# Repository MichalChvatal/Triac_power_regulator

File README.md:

# AVR Triac Regulator (ATtiny13)

---

## ⚠️ Safety Disclaimer

This project involves **AC mains voltage**, which is **extremely dangerous** and can cause **serious injury or death**.  

By using this project, you accept **full responsibility** for any accidents, injuries, or damages. The author is **not liable** for any consequences resulting from its use.  

**Important Safety Guidelines:**
- Always use insulated tools and protective equipment.
- Work with a qualified professional if you are inexperienced with mains circuits.
- Use galvanic isolation (optotriacs/optocouplers) wherever possible.
- **Do not proceed** if you are unfamiliar with handling high voltage.

---

## Project Overview

This project implements a **power regulator for universal commutator motors** (motors with brushes) and resistive loads (e.g., light bulbs and heating elements) using the **ATtiny13** microcontroller.  
It provides **0–100% power control** through **phase-angle control of a triac** with **AC mains zero-cross detection**.

⚠️ **Warning:** The circuit connects directly to **230 V mains**. Extreme caution is required during assembly and testing.

---

## ✨ Features
- Measurement of the delay between zero-crossing and triac triggering.
- Adjustable firing angle using a potentiometer (or DIP switch).
- Generation of a trigger pulse for the optotriac in every half cycle.
- Motor power control from **fully OFF (0%)** to **fully ON (100%)**.

---

## 🧩 Components

### Triac driver (optotriac)
Must be of the **random-phase type** (no built-in zero-cross detection), e.g.:
- `MOC3021`
- `MOC3010`

### Zero-cross detector
The output must be a **rectangular pulse signal** for reliable edge detection by the MCU, e.g.:
- `H11L1` (recommended)

If using slower optocouplers such as `4N35`, you must add a **Schmitt trigger** circuit to clean up the signal.

### Microcontroller
- `ATtiny13` (or alternatively `ATmega8`)

### Firing angle adjustment
- **Potentiometer** (connected to ADC input)  
- or **DIP switch** (digital inputs)

---

## ⚡ Safety notes
- This regulator is suitable only for **universal commutator motors (brush motors)** and **resistive loads** (e.g., light bulbs and heating elements).
- It is **not suitable for asynchronous (induction) motors**.  
- The motor must **not** have its own built-in electronic regulation.  
- The motor must use **series excitation**.

---

## 🛠️ Project directory structure

- **HW/** – Eagle PCB design files (.sch, .brd)
- **SW/**  - Atmel Studio project files (.cproj, .atsln), Doxyfile
  - **src/** – Source files (.c)
  - **inc/** – Header files (.h)
  - **docs/** – Generated documentation (Doxygen)

---

## ⚙️ Fuse and clock configuration

- Set fuses for **internal oscillator 4.8 MHz**:  
  - **Low fuse:** `0x79`  
  - **High fuse:** `0xFF`  
- ⚠️ **Calibration is required** – see ATtiny13 datasheet for details.  
- Note: `clk I/O` = `clk CPU`. The difference is that during sleep mode, **I/O clocks are disabled**, while CPU/peripheral clocks may continue to run.

--- 

## 🔧 Building the Project
To build the project, launch the **Regulator.atsln** file with **Microchip Studio (version 7.0.2594)**.

- From the menu bar, select Build > Build Solution.
-  Alternatively, use the shortcut F7.

The output files will be located in the project's **Debug** or **Release** folder.

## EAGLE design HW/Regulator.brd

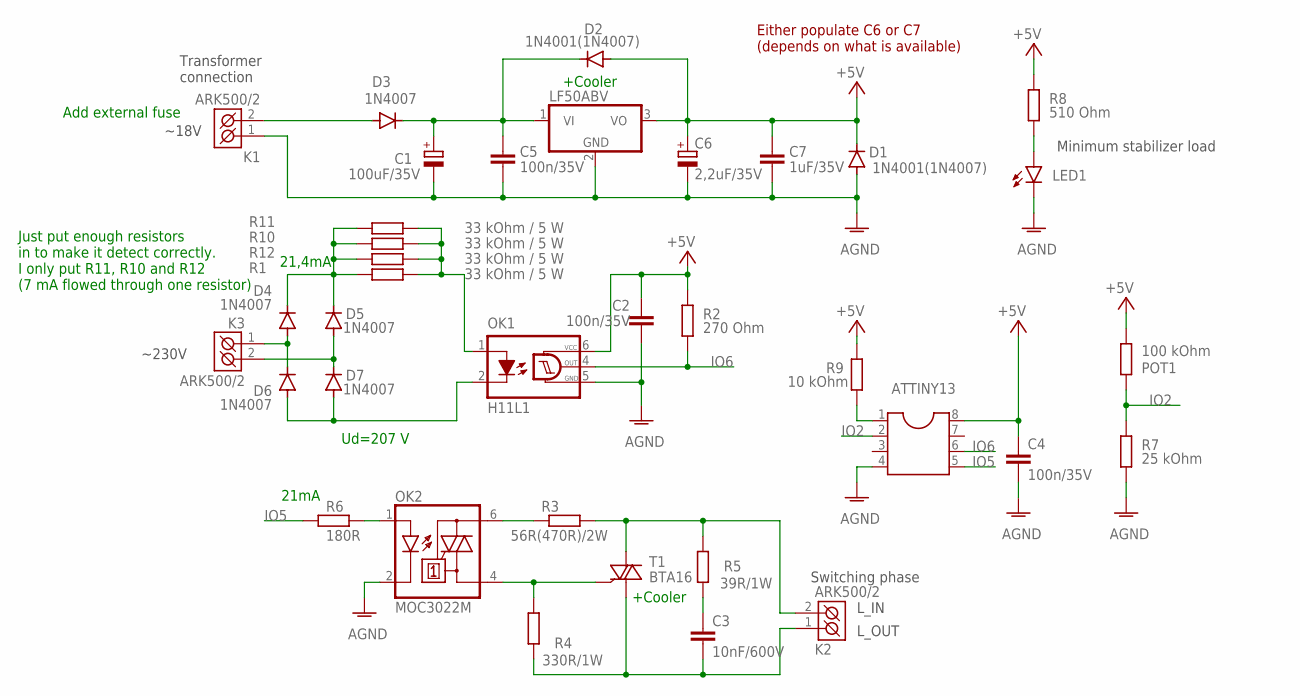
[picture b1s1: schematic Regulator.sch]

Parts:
ATTINY13: DIL8S; SOCKET-08
C1: 100uF/35V; E3,5-8
C2, C4, C5: 100n/35V; C050-025X075
C3: 10nF/600V; C025-030X050
C6: 2,2uF/35V; E2-4
C7: 1uF/35V; C050-025X075
D1, D2: 1N4001(1N4007); DO41-7.6
D3, D4, D5, D6, D7: 1N4007; DO41-7.6
K1, K2, K3: ARK500/2
LED1: LED5MM
OK1: H11L1; DIL06
OK2: MOC3022M; DIL06
POT1: 100 kOhm; 0207/10
R1, R10, R11, R12: 33 kOhm / 5 W; 0617V
R2: 270 Ohm; 0207/10
R3: 56R(470R)/2W; 0411/15
R4: 330R/1W; 0411/15
R5: 39R/1W; 0411/15
R6: 180R; 0207/10
R7: 25 kOhm; 0207/10
R8: 510 Ohm; 0207/10
R9: 10 kOhm; 0207/10
ST1: LF50ABV; TO220V
T1: BTA16; TO220BV

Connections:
+5V: ATTINY13.8, C2.1, C4.1, C6.+, C7.1, D1.C, D2.A, OK1.6 (VCC), POT1.1, R2.1, R8.1, R9.1, ST1.3 (VO)
AGND: ATTINY13.4, C1.-, C2.2, C4.2, C5.2, C6.-, C7.2, D1.A, K1.1 (K1), LED1.K (C), OK1.5 (GND), OK2.2 (C), R7.2, ST1.2 (GND)
IO2: ATTINY13.2, POT1.2, R7.1
IO5: ATTINY13.5, R6.1
IO6: ATTINY13.6, OK1.4 (OUT), R2.2
L_IN: K2.2 (K2), R3.2, R5.2, T1.T2 (A2)
L_OUT: C3.2, K2.1 (K1), R4.1, T1.T1 (A1)
unnamed: OK1.1 (A), R1.2, R10.2, R11.2, R12.2
unnamed: D4.A, D6.C, K3.1 (K1)
unnamed: LED1.A, R8.2
unnamed: D3.A, K1.2 (K2)
unnamed: OK2.6 (A2), R3.1
unnamed: D6.A, D7.A, OK1.2 (C)
unnamed: D5.A, D7.C, K3.2 (K2)
unnamed: C1.+, C5.1, D2.C, D3.C, ST1.1 (VI)
unnamed: OK2.1 (A), R6.2
unnamed: C3.1, R5.1
unnamed: OK2.4 (A1), R4.2, T1.G
unnamed: ATTINY13.1, R9.2
unnamed: D4.C, D5.C, R1.1, R10.1, R11.1, R12.1

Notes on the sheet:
Add external fuse
+Cooler
21mA
21,4mA
Either populate C6 or C7 (depends on what is available)
Minimum stabilizer load
L_IN
L_OUT
~18V
Switching phase
Transformer connection
~230V
Ud=207 V
Just put enough resistors in to make it detect correctly. I only put R11, R10 and R12 (7 mA flowed through one resistor)

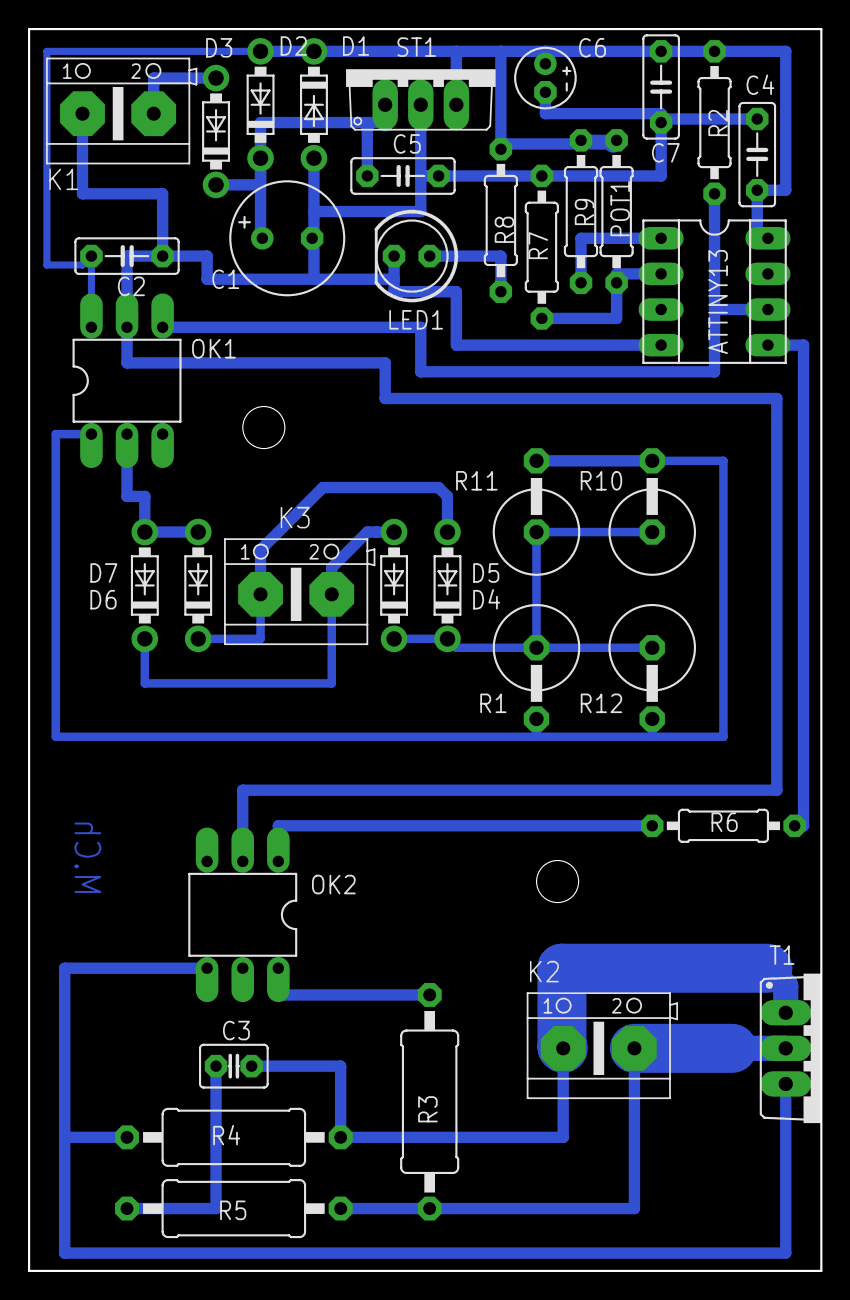
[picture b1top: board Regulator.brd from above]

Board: 2 copper layers, 56.5 x 88.6 mm, 36 parts (0 on the bottom side), 20 nets.

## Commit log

2025-08-22 version 1.0

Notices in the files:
parts and their libraries:
Copyright (C) PaJa 2011-2014
